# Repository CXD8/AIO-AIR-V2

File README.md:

# AIO-AIR-V2

A compact ESP32 based air-quality monitor combining dedicated sensors for CO₂, particulate matter, VOCs, NOx, temperature and humidity.
# PCB

# Assembly

# Schematic

## Features

- **True NDIR CO₂ measurement w/ temperature and humidity** Sensirion SCD30
- **Particulate monitoring** Sensirion SPS30
  - PM1.0
  - PM2.5
  - PM4.0
  - PM10
- **VOC & NOx monitoring** Sensirion SGP41
- **240×320 colour TFT display**
- **ESP32-S3 powered**
- **Wi-Fi connectivity**
- **Home Assistant integration**
  - Live sensor data
  - Individual sensor controls
  - Remote sensor enable/disable
  - Historical data
- **Real-time air-quality status indicators**
- **Compact all-in-one design**

## How to Use

### 1. Flash the Firmware using Ardiuno IDE

### 2. Connect the Sensors
Solder connections respectively from the sensors TX to RX, GND to GND, POWER to POWER as per silkscreen.

### 3. Configure Wi-Fi

Enter your Wi-Fi credentials in the firmware configuration

Flash the firmware after changing the credentials.

### 3. Home Assistant
Once connected to Wi-Fi, the device can be added to **Home Assistant**.

Home Assistant provides access to the sensor readings and allows supported sensor settings to be changed remotely, including:

- Sensor enable/disable
- Historical data
- more

| Item | References | Value | Footprint | Quantity | Unit Price (USD) | Total (USD) | Link |
|---:|:---|:---|:---|---:|---:|---:|:---|
| 1 | C1, C4, C6, C9, C11, C13, C14, C16, C19 | CL10B104KB8NNNC | CL10B104KB8NNNC | 9 | $0.0082 | $0.0738 | [LCSC](https://www.lcsc.com/product-detail/C1591.html) |
| 2 | C2, C10, C17, C18 | CL10A106KP8NNNC | CL10A106KP8NNNC | 4 | $0.0308 | $0.1232 | [LCSC](https://www.lcsc.com/product-detail/C19702.html) |
| 3 | C5, C7, C12, C15 | CL10A226MP8NUNE | CL10A226MP8NUNE | 4 | $0.0435 | $0.1740 | [LCSC](https://www.lcsc.com/product-detail/C86295.html) |
| 4 | R1, R4 | RC0603FR-0710KL | RC0603FR-0710KL | 2 | $0.0034 | $0.0068 | [LCSC](https://www.lcsc.com/product-detail/C98220.html) |
| 5 | R2, R3 | RC0603FR-075K1L | RC0603FR-075K1L | 2 | $0.0023 | $0.0046 | [LCSC](https://www.lcsc.com/product-detail/C105580.html) |
| 7 | U1 | ESP32-WROOM-32U_8MB | ESP32-WROOM-32U_8MB | 1 | $4.5341 | $4.5341 | [LCSC](https://www.lcsc.com/product-detail/C328062.html) |
| 8 | U2 | AP2114H-3_3TRG1 | AP2114H-3_3TRG1 | 1 | $0.2319 | $0.2319 | [LCSC](https://www.lcsc.com/product-detail/C150716.html) |
| 10 | U5 | DISPLAY | 2_54-1_4 | 1 | $8.50 | $8.50 | [AliExpress](https://www.aliexpress.com/item/1005012793358185.html) |
| 12 | SW1 | TS-1088-AR02016 | TS-1088-AR02016 | 1 | $0.0504 | $0.0504 | [LCSC](https://www.lcsc.com/product-detail/C720477.html) |
| 13 | CN1 | SGP41 | PH2_0-4P | 1 | $9.01 | $9.01 | [Sensirion](https://sensirion.com/products/catalog/SGP41) |
| 14 | CN2 | SCD30 | B5B-PH-K-S-_LF_SN | 1 | $47.36 | $47.36 | [Sensirion](https://sensirion.com/products/catalog/SCD30) |
| 15 | CN3 | SPS30 | B5B-PH-K-S-_LF_SN | 1 | $38.99 | $38.99 | [Sensirion](https://sensirion.com/products/catalog/SPS30) |
| 16 | CN4 | LUX SENSOR | B5B-PH-K-S-_LF_SN | 1 | $2.10 | $2.10 | [AliExpress](https://www.aliexpress.com/item/1005007790877449.html) |
| 17 | USB1 | TYPE-C_16P_QTWT | TYPE-C_16P_QTWT | 1 | $0.0713 | $0.0713 | [LCSC](https://www.lcsc.com/product-detail/C5187472.html) |
| **TOTAL** | | | | **30** | | **$111.23** | |

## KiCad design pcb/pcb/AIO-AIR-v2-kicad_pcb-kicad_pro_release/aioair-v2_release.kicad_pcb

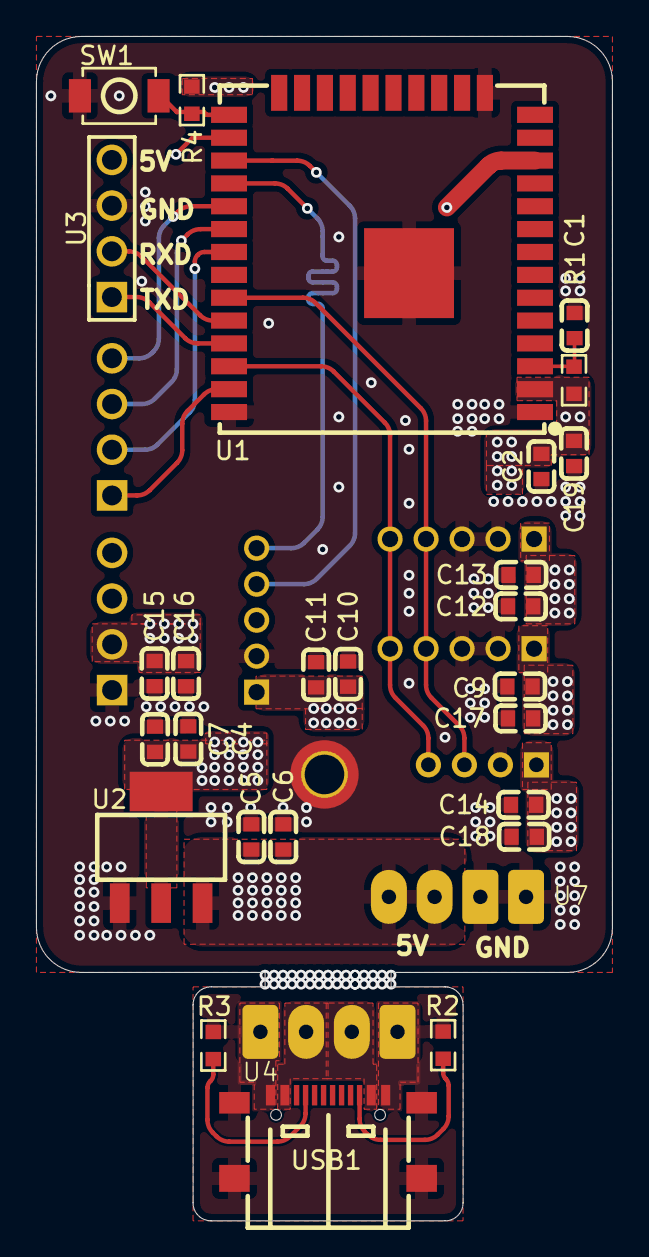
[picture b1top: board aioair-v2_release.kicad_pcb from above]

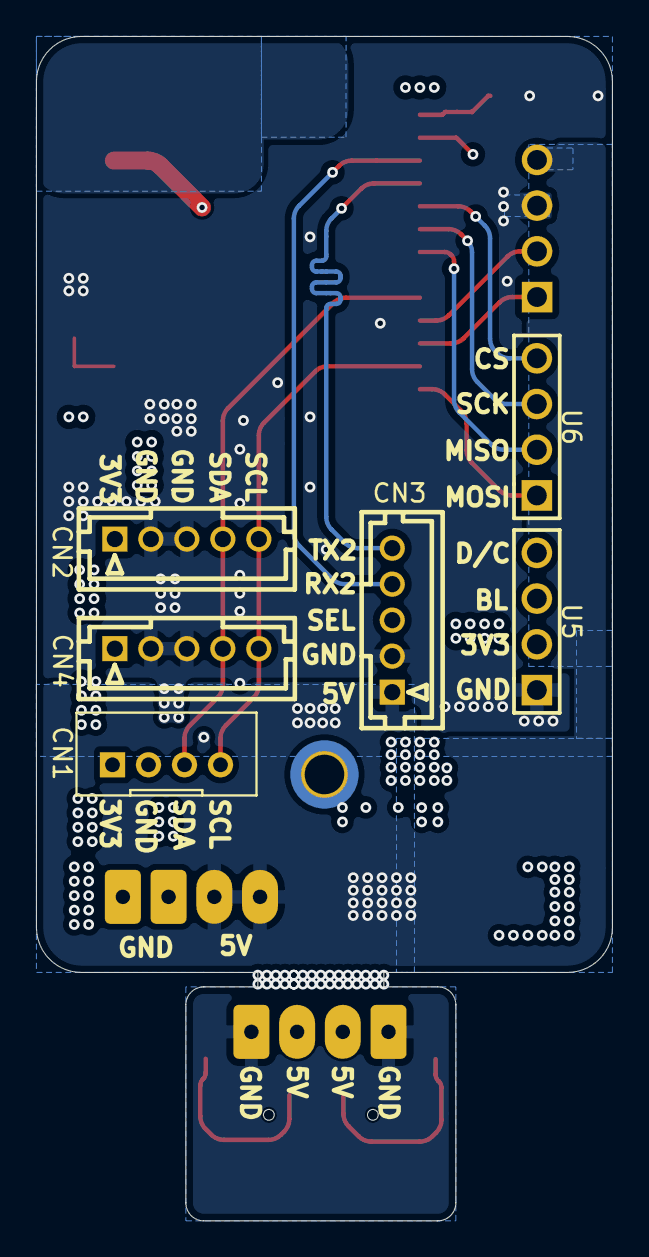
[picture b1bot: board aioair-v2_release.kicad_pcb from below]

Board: 4 copper layers, 32.0 x 65.8 mm, 34 parts (6 on the bottom side), 19 nets.

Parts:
C1, C4, C6, C9, C11, C13, C14, C16, C19: CL10B104KB8NNNC
C2, C10, C17, C18: CL10A106KP8NNNC
C5, C7, C12, C15: CL10A226MP8NUNE
CN1: SGP41; PH2_0-4P
CN2: SCD30; B5B-PH-K-S-_LF_SN
CN3: SPS30; B5B-PH-K-S-_LF_SN
CN4: LUX SENSOR; B5B-PH-K-S-_LF_SN
R1, R4: RC0603FR-0710KL
R2, R3: RC0603FR-075K1L
SW1: TS-1088-AR02016
U1: ESP32-WROOM-32U_8MB
U2: AP2114H-3_3TRG1
U3: UART DOWNLOAD; 2_54-1_4
U4, U7: power_1
U5: DISPLAY_1; 2_54-1_4
U6: DISPLAY_2; 2_54-1_4
USB1: TYPE-C_16P_QTWT

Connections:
+3V3: C2.1, C4.2, C7.1, C9.2, C12.1, C13.2, C14.2, C15.1, C16.2, C17.2, C18.2, C19.1, CN1.1, CN2.1, CN4.1, R1.2, R4.2, U1.2 (VDD33), U2.2 (VOUT), U2.4 (VOUT), U5.2
+5V: C5.1, C6.2, C10.2, C11.2, CN3.1, U2.3 (VIN), U3.4, U4.3 (5V), U7.3 (5V), USB1.A4B9 (VBUS), USB1.B4A9 (VBUS)
/BL: U1.12 (IO27), U5.3
/CS: U1.29 (IO5), U6.4
/D/C: U1.26 (IO4), U5.4
/IO0: R4.1, SW1.1, U1.25 (IO0)
/MISO: U1.31 (IO19), U6.2
/MOSI: U1.37 (IO23), U6.1
/RX2: CN3.4, U1.27 (IO16)
/RXD: U1.34 (RXD0), U3.2
/SCK: U1.30 (IO18), U6.3
/SCL: CN1.4, CN2.5, CN4.5, U1.36 (IO22)
/SDA: CN1.3, CN2.4, CN4.4, U1.33 (IO21)
/TX2: CN3.5, U1.28 (IO17)
/TXD: U1.35 (TXD0), U3.1
GND: C1.1, C2.2, C4.1, C5.2, C6.1, C7.2, C9.1, C10.1, C11.1, C12.2, C13.1, C14.1, C15.2, C16.1, C17.1, C18.1, C19.2, CN1.2, CN2.2, CN2.3, CN3.2, CN4.2, CN4.3, R2.1, R3.1, SW1.2, U1.1 (GND), U1.15 (GND), U1.38 (GND), U1.39 (GND), U2.1 (GND), U3.3, U4.1 (GND), U4.2 (GND), U5.1, U7.1 (GND), U7.2 (GND), USB1.0 (EH), USB1.A1B12 (GND), USB1.B1A12 (GND)
unnamed: C1.2, R1.1, U1.3 (EN)
unnamed: R3.2, USB1.A5 (CC1)
unnamed: R2.2, USB1.B5 (CC2)

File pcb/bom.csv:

Item,References,Value,Footprint,Quantity,Link
1,"C1, C4, C6, C9, C11, C13, C14, C16, C19",CL10B104KB8NNNC,CL10B104KB8NNNC,9,https://www.lcsc.com/product-detail/C1591.html
2,"C2, C10, C17, C18",CL10A106KP8NNNC,CL10A106KP8NNNC,4,https://www.lcsc.com/product-detail/C19702.html
3,"C5, C7, C12, C15",CL10A226MP8NUNE,CL10A226MP8NUNE,4,https://www.lcsc.com/product-detail/C86295.html
4,"R1, R4",RC0603FR-0710KL,RC0603FR-0710KL,2,https://www.lcsc.com/product-detail/C98220.html
5,"R2, R3",RC0603FR-075K1L,RC0603FR-075K1L,2,https://www.lcsc.com/product-detail/C105580.html
6,"U4, U7",~,power_1,2,
7,U1,ESP32-WROOM-32U_8MB,ESP32-WROOM-32U_8MB,1,https://www.lcsc.com/product-detail/C328062.html
8,U2,AP2114H-3_3TRG1,AP2114H-3_3TRG1,1,https://www.lcsc.com/product-detail/C150716.html
9,U3,UART DOWNLOAD,2_54-1_4,1,
10,U5,DISPLAY_1,2_54-1_4,1,https://www.aliexpress.com/item/1005012793358185.html
11,U6,DISPLAY_2,2_54-1_4,1,https://www.aliexpress.com/item/1005012793358185.html
12,SW1,TS-1088-AR02016,TS-1088-AR02016,1,https://www.lcsc.com/product-detail/C720477.html
13,CN1,SGP41,PH2_0-4P,1,https://sensirion.com/products/catalog/SGP41
14,CN2,SCD30,B5B-PH-K-S-_LF_SN,1,https://sensirion.com/products/catalog/SCD30
15,CN3,SPS30,B5B-PH-K-S-_LF_SN,1,https://sensirion.com/products/catalog/SPS30
16,CN4,LUX SENSOR,B5B-PH-K-S-_LF_SN,1,https://www.aliexpress.com/item/1005007790877449.html
17,USB1,TYPE-C_16P_QTWT,TYPE-C_16P_QTWT,1,https://www.lcsc.com/product-detail/C5187472.html
